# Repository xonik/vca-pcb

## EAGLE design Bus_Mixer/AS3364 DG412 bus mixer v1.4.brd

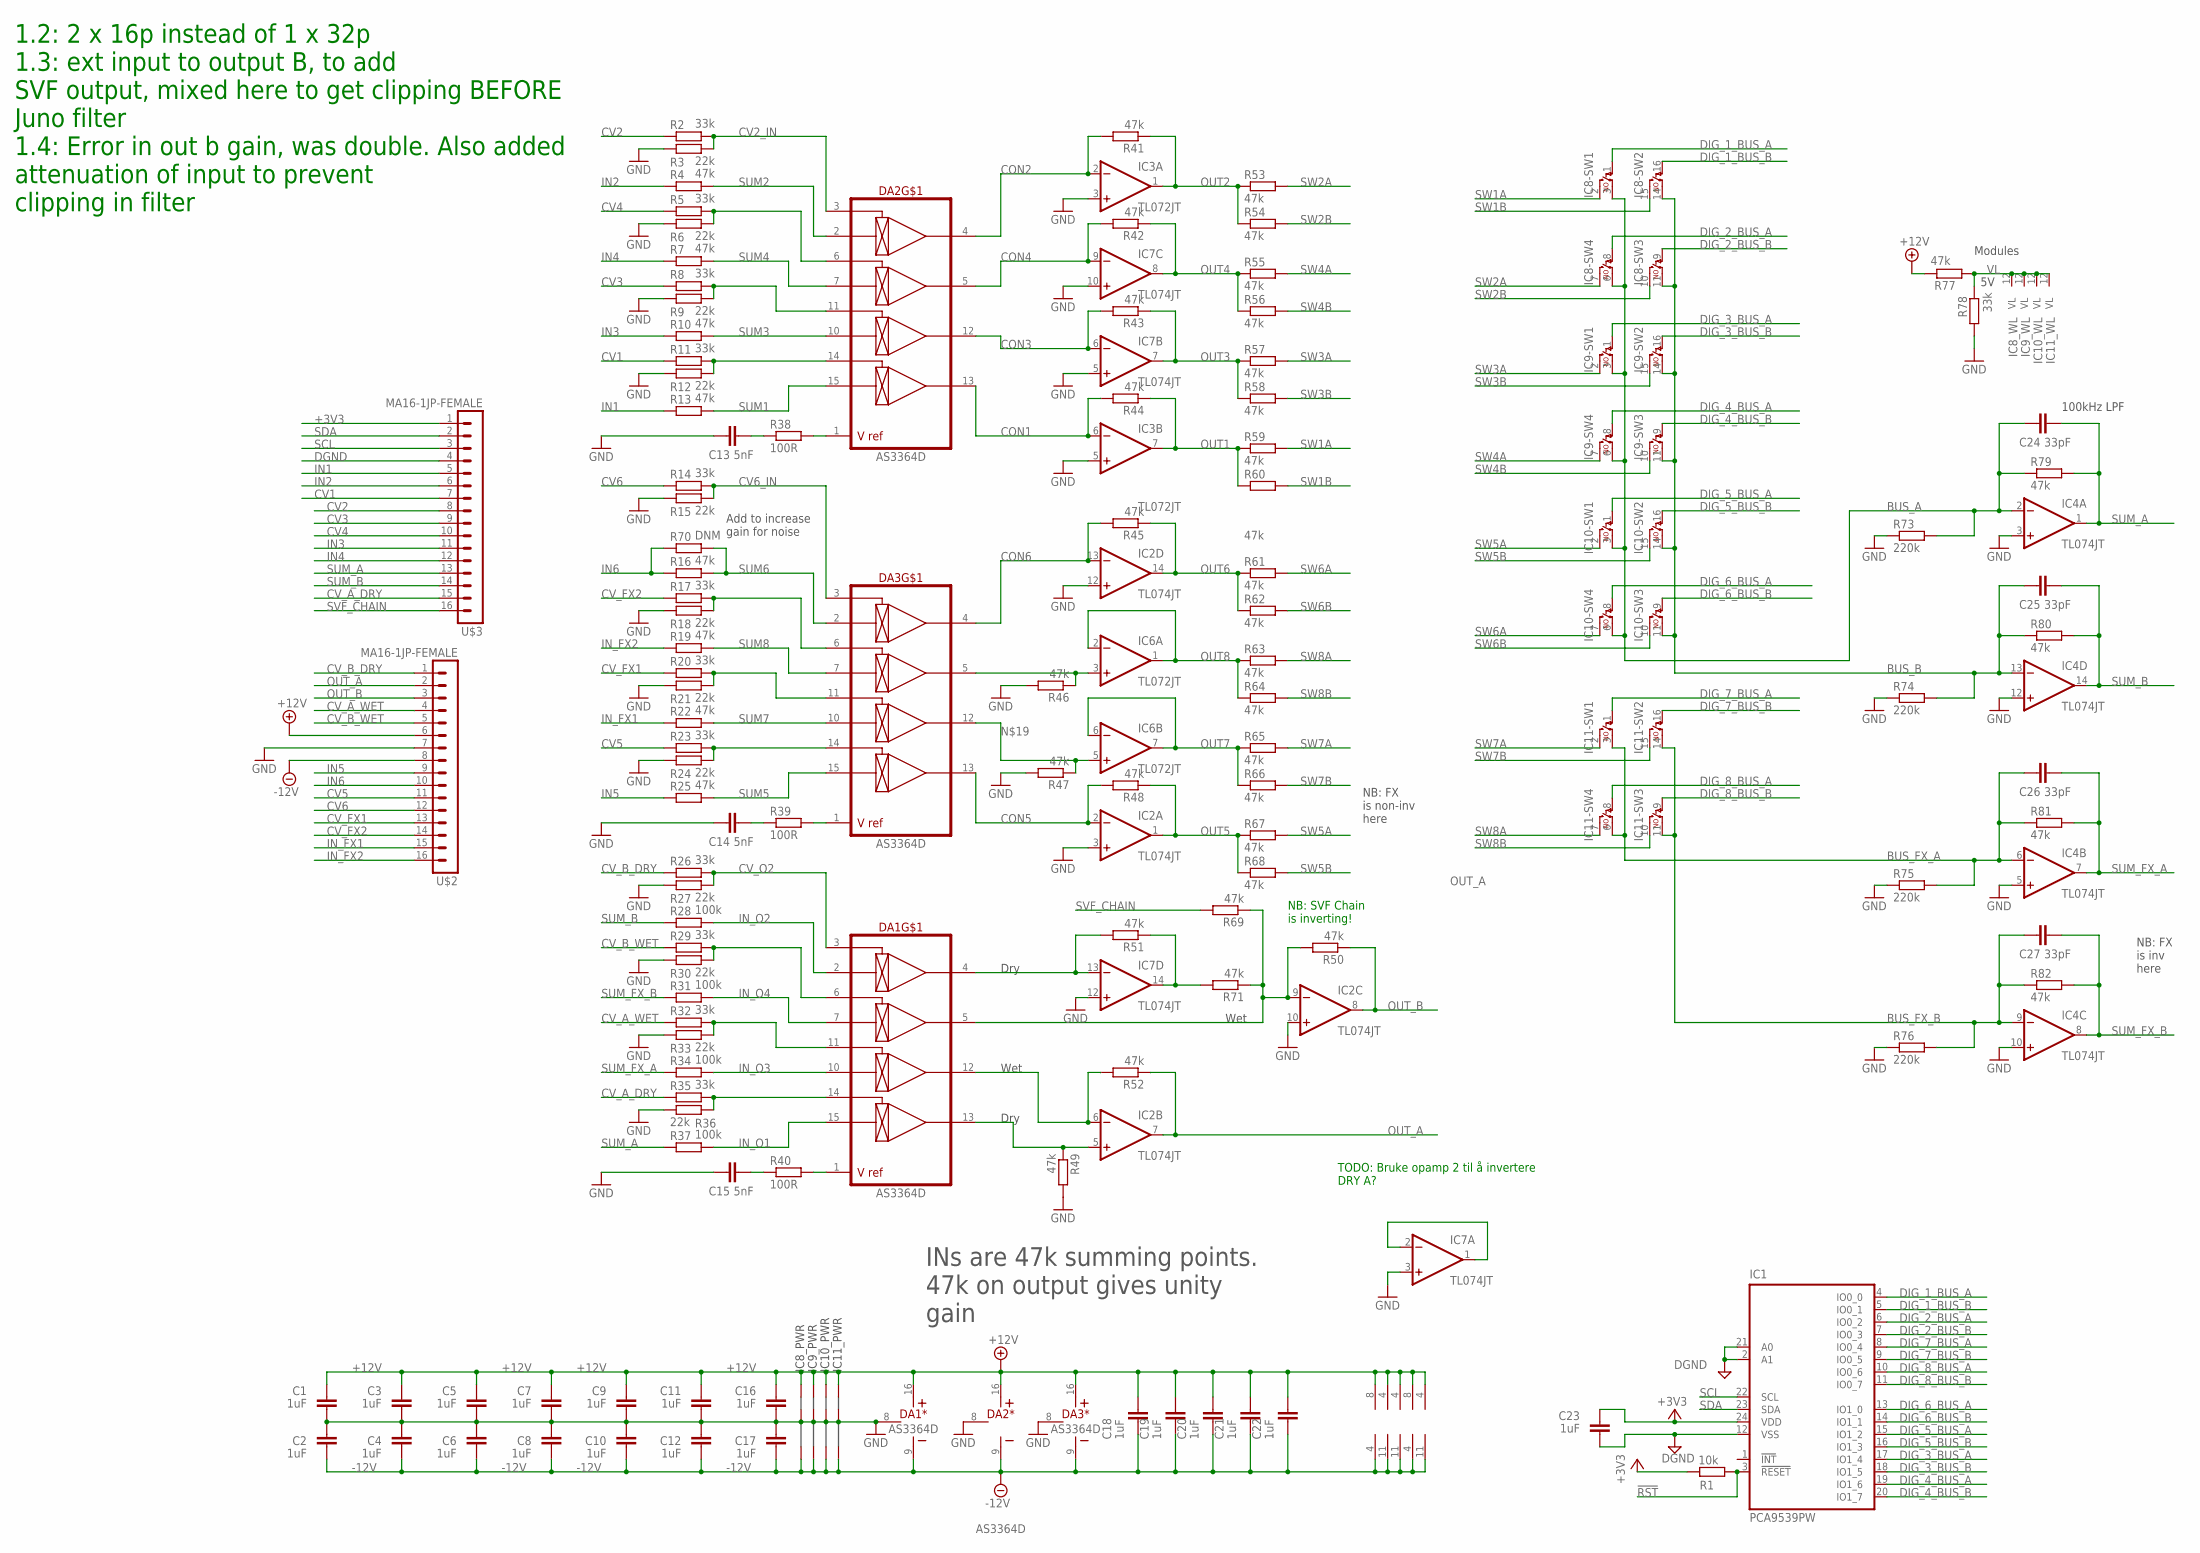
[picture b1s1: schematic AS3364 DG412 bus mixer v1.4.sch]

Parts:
C1, C2, C3, C4, C5, C6, C7, C8, C9, C10, C11, C12, C16, C17: 1uF; C0402-J
C13, C14, C15: 5nF; C0402-J
C18, C19, C20, C21, C22, C23: 1uF; C0402
C24, C25, C26, C27: 33pF; C0402-J
DA1, DA2, DA3: AS3364D; DIL16J
IC1: PCA9539PW; TSSOP24J
IC2, IC4, IC7: TL074JT; TSSOP14J
IC3, IC6: TL072JT; TSSOP8J
IC8, IC9, IC10, IC11: DG412-J; DIL16J
R1: 10k; R0402
R2, R5, R8, R11, R14, R17, R20, R23, R26, R29, R32, R35, R78: 33k; R0402
R3, R6, R9, R12, R15, R18, R21, R24, R27, R30, R33, R36: 22k; R0402
R4, R7, R10, R13, R16, R19, R22, R25, R41, R42, R43, R44, R45, R46, R47, R48, R49, R50, R51, R52, R53, R54, R55, R56, R57, R58, R59, R60, R61, R62, R63, R64, R65, R66, R67, R68, R69, R71, R77, R79, R80, R81, R82: 47k; R0402
R28, R31, R34, R37: 100k; R0402
R38, R39, R40: 100R; R0402
R70: DNM; R0805
R73, R74, R75, R76: 220k; R0603
U$2, U$3: MA16-1JP-FEMALE; SIP-PIN16-1J

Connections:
!RST: IC1.3 (!RESET), R1.2
+3V3: C23.2, IC1.24 (VDD), R1.1, U$3.1
+12V: C1.2, C3.2, C5.2, C7.2, C9.2, C11.2, C16.2, C18.2, C19.2, C20.2, C21.2, C22.2, DA1.16 (V+), DA2.16 (V+), DA3.16 (V+), IC2.4 (V+), IC3.8 (V+), IC4.4 (V+), IC6.8 (V+), IC7.4 (V+), IC8.13 (+15V), IC9.13 (+15V), IC10.13 (+15V), IC11.13 (+15V), R77.1, U$2.6
-12V: C2.1, C4.1, C6.1, C8.1, C10.1, C12.1, C17.1, C18.1, C19.1, C20.1, C21.1, C22.1, DA1.9 (V-), DA2.9 (V-), DA3.9 (V-), IC2.11 (V-), IC3.4 (V-), IC4.11 (V-), IC6.4 (V-), IC7.11 (V-), IC8.4 (-15V), IC9.4 (-15V), IC10.4 (-15V), IC11.4 (-15V), U$2.8
BUS_A: C24.1, IC4.2 (-IN), IC8.3 (S), IC8.6 (S), IC9.3 (S), IC9.6 (S), IC10.3 (S), IC10.6 (S), R73.2, R79.1
BUS_B: C25.1, IC4.13 (-IN), IC8.11 (S), IC8.14 (S), IC9.11 (S), IC9.14 (S), IC10.11 (S), IC10.14 (S), R74.2, R80.1
BUS_FX_A: C26.1, IC4.6 (-IN), IC11.3 (S), IC11.6 (S), R75.2, R81.1
BUS_FX_B: C27.1, IC4.9 (-IN), IC11.11 (S), IC11.14 (S), R76.2, R82.1
CON1: DA2.13 (OUT4), IC3.6 (-IN), R44.2
CON2: DA2.4 (OUT1), IC3.2 (-IN), R41.2
CON3: DA2.12 (OUT3), IC7.6 (-IN), R43.2
CON4: DA2.5 (OUT2), IC7.9 (-IN), R42.2
CON5: DA3.13 (OUT4), IC2.2 (-IN), R48.2
CON6: DA3.4 (OUT1), IC2.13 (-IN), R45.2
CON_O1: DA1.12 (OUT3), IC2.6 (-IN), R52.2
CV1: R11.1, U$3.7
CV2: R2.1, U$3.8
CV2_IN: DA2.3 (CV1), R2.2, R3.2
CV3: R8.1, U$3.9
CV4: R5.1, U$3.10
CV5: R23.1, U$2.11
CV6: R14.1, U$2.12
CV6_IN: DA3.3 (CV1), R14.2, R15.2
CV_A_DRY: R35.1, U$3.15
CV_A_WET: R32.1, U$2.4
CV_B_DRY: R26.1, U$2.1
CV_B_WET: R29.1, U$2.5
CV_FX1: R20.1, U$2.13
CV_FX2: R17.1, U$2.14
CV_O2: DA1.3 (CV1), R26.2, R27.2
DGND: C23.1, IC1.2 (A1), IC1.12 (VSS), IC1.21 (A0), U$3.4
DIG_1_BUS_A: IC1.4 (IO0_0), IC8.1 (C)
DIG_1_BUS_B: IC1.5 (IO0_1), IC8.16 (C)
DIG_2_BUS_A: IC1.6 (IO0_2), IC8.8 (C)
DIG_2_BUS_B: IC1.7 (IO0_3), IC8.9 (C)
DIG_3_BUS_A: IC1.17 (IO1_4), IC9.1 (C)
DIG_3_BUS_B: IC1.18 (IO1_5), IC9.16 (C)
DIG_4_BUS_A: IC1.19 (IO1_6), IC9.8 (C)
DIG_4_BUS_B: IC1.20 (IO1_7), IC9.9 (C)
DIG_5_BUS_A: IC1.15 (IO1_2), IC10.1 (C)
DIG_5_BUS_B: IC1.16 (IO1_3), IC10.16 (C)
DIG_6_BUS_A: IC1.13 (IO1_0), IC10.8 (C)
DIG_6_BUS_B: IC1.14 (IO1_1), IC10.9 (C)
DIG_7_BUS_A: IC1.8 (IO0_4), IC11.1 (C)
DIG_7_BUS_B: IC1.9 (IO0_5), IC11.16 (C)
DIG_8_BUS_A: IC1.10 (IO0_6), IC11.8 (C)
DIG_8_BUS_B: IC1.11 (IO0_7), IC11.9 (C)
GND: C1.1, C2.2, C3.1, C4.2, C5.1, C6.2, C7.1, C8.2, C9.1, C10.2, C11.1, C12.2, C13.1, C14.1, C15.1, C16.1, C17.2, DA1.8 (GND), DA2.8 (GND), DA3.8 (GND), IC2.3 (+IN), IC2.10 (+IN), IC2.12 (+IN), IC3.3 (+IN), IC3.5 (+IN), IC4.3 (+IN), IC4.5 (+IN), IC4.10 (+IN), IC4.12 (+IN), IC7.3 (+IN), IC7.5 (+IN), IC7.10 (+IN), IC7.12 (+IN), IC8.5 (AGND), IC9.5 (AGND), IC10.5 (AGND), IC11.5 (AGND), R3.1, R6.1, R9.1, R12.1, R15.1, R18.1, R21.1, R24.1, R27.1, R30.1, R33.1, R36.1, R46.2, R47.2, R49.2, R73.1, R74.1, R75.1, R76.1, R78.2, U$2.7
IN1: R13.1, U$3.5
IN2: R4.1, U$3.6
IN3: R10.1, U$3.11
IN4: R7.1, U$3.12
IN5: R25.1, U$2.9
IN6: R16.1, R70.1, U$2.10
IN_FX1: R22.1, U$2.15
IN_FX2: R19.1, U$2.16
IN_O1: DA1.15 (IN4), R37.2
IN_O2: DA1.2 (IN1), R28.2
IN_O3: DA1.10 (IN3), R34.2
IN_O4: DA1.7 (IN2), R31.2
unnamed: DA3.1 (VREF), R39.2
unnamed: DA2.1 (VREF), R38.2
unnamed: DA3.6 (CV2), R17.2, R18.2
unnamed: DA3.5 (OUT2), IC6.3 (+IN), R46.1
unnamed: DA3.11 (CV3), R20.2, R21.2
unnamed: DA1.5 (OUT2), IC2.9 (-IN), R50.2, R69.1, R71.1
unnamed: DA3.14 (CV4), R23.2, R24.2
unnamed: C14.2, R39.1
unnamed: DA1.1 (VREF), R40.2
unnamed: DA2.6 (CV2), R5.2, R6.2
unnamed: DA1.6 (CV2), R29.2, R30.2
unnamed: DA2.11 (CV3), R8.2, R9.2
unnamed: DA1.11 (CV3), R32.2, R33.2
unnamed: C13.2, R38.1
unnamed: DA1.14 (CV4), R35.2, R36.2
unnamed: C15.2, R40.1
unnamed: DA1.4 (OUT1), IC7.13 (-IN), R51.2
unnamed: DA1.13 (OUT4), IC2.5 (+IN), R49.1
unnamed: DA3.12 (OUT3), IC6.5 (+IN), R47.1
unnamed: IC7.14 (OUT), R51.1, R71.2
unnamed: DA2.14 (CV4), R11.2, R12.2
unnamed: IC7.1 (OUT), IC7.2 (-IN)
OUT1: IC3.7 (OUT), R44.1, R59.1, R60.1
OUT2: IC3.1 (OUT), R41.1, R53.1, R54.1
OUT3: IC7.7 (OUT), R43.1, R57.1, R58.1
OUT4: IC7.8 (OUT), R42.1, R55.1, R56.1
OUT5: IC2.1 (OUT), R48.1, R67.1, R68.1
OUT6: IC2.14 (OUT), R45.1, R61.1, R62.1
OUT7: IC6.6 (-IN), IC6.7 (OUT), R65.1, R66.1
OUT8: IC6.1 (OUT), IC6.2 (-IN), R63.1, R64.1
OUT_A: IC2.7 (OUT), R52.1, U$2.2
OUT_B: IC2.8 (OUT), R50.1, U$2.3
SCL: IC1.22 (SCL), U$3.3
SDA: IC1.23 (SDA), U$3.2
SUM1: DA2.15 (IN4), R13.2
SUM2: DA2.2 (IN1), R4.2
SUM3: DA2.10 (IN3), R10.2
SUM4: DA2.7 (IN2), R7.2
SUM5: DA3.15 (IN4), R25.2
SUM6: DA3.2 (IN1), R16.2, R70.2
SUM7: DA3.10 (IN3), R22.2
SUM8: DA3.7 (IN2), R19.2
SUM_A: C24.2, IC4.1 (OUT), R37.1, R79.2, U$3.13
SUM_B: C25.2, IC4.14 (OUT), R28.1, R80.2, U$3.14
SUM_FX_A: C26.2, IC4.7 (OUT), R34.1, R81.2
SUM_FX_B: C27.2, IC4.8 (OUT), R31.1, R82.2
SVF_CHAIN: R69.2, U$3.16
SW1A: IC8.2 (D), R59.2
SW1B: IC8.15 (D), R60.2
SW2A: IC8.7 (D), R53.2
SW2B: IC8.10 (D), R54.2
SW3A: IC9.2 (D), R57.2
SW3B: IC9.15 (D), R58.2
SW4A: IC9.7 (D), R55.2
SW4B: IC9.10 (D), R56.2
SW5A: IC10.2 (D), R67.2
SW5B: IC10.15 (D), R68.2
SW6A: IC10.7 (D), R61.2
SW6B: IC10.10 (D), R62.2
SW7A: IC11.2 (D), R65.2
SW7B: IC11.15 (D), R66.2
SW8A: IC11.7 (D), R63.2
SW8B: IC11.10 (D), R64.2
VL: IC8.12 (VL), IC9.12 (VL), IC10.12 (VL), IC11.12 (VL), R77.2, R78.1

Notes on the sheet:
INs are 47k summing points. 47k on output gives unity gain
Modules
100kHz LPF
Wet
Dry
NB: FX is non-inv here
NB: FX is inv here
1.2: 2 x 16p instead of 1 x 32p 1.3: ext input to output B, to add SVF output, mixed here to get clipping BEFORE Juno filter 1.4: Error in out b gain, was double. Also added attenuation of input to prevent clipping in filter
NB: SVF Chain is inverting!
Add to increase gain for noise
TODO: Bruke opamp 2 til å invertere DRY A?

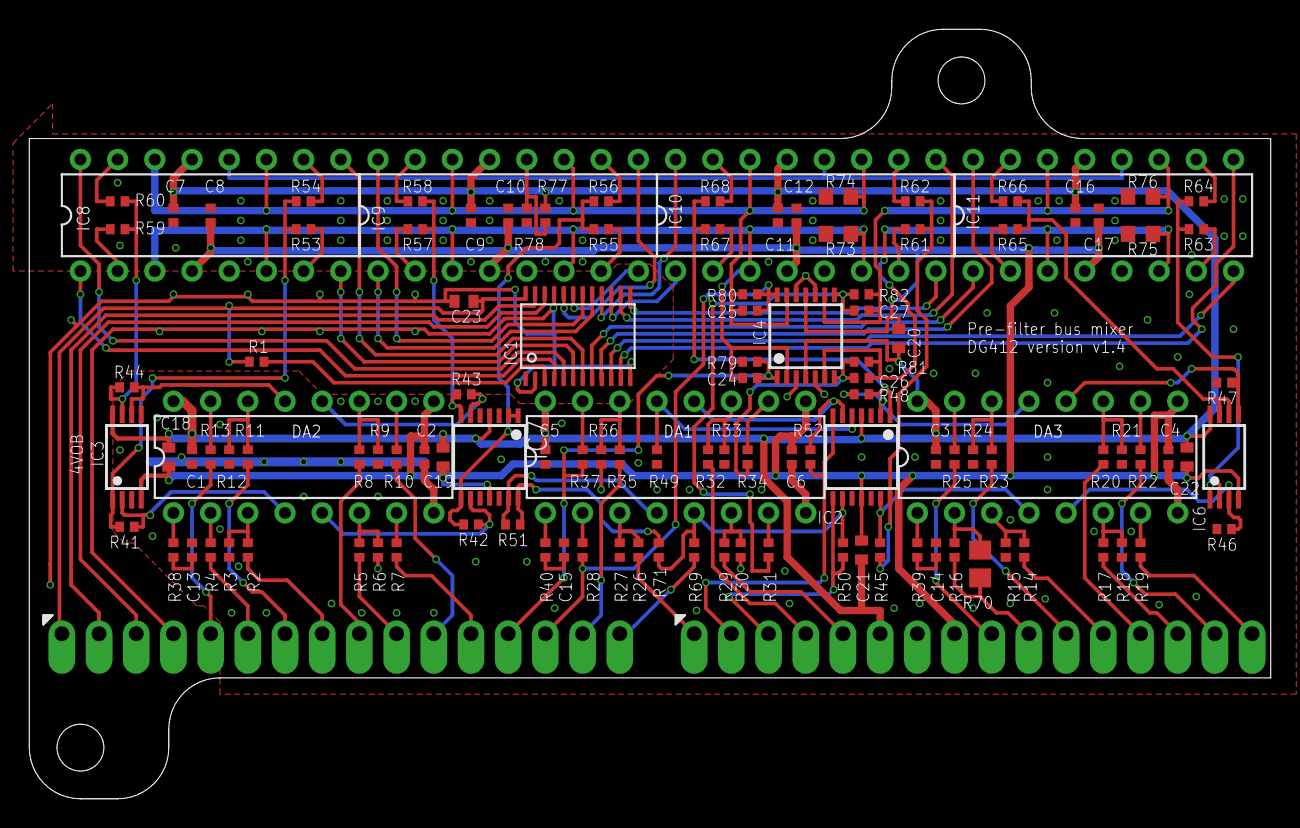
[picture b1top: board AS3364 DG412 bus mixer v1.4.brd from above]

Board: 2 copper layers, 84.8 x 52.5 mm, 124 parts (1 on the bottom side), 124 nets.

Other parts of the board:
U$1: XONIK_LOGO_35

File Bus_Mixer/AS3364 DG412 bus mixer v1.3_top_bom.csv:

Comment,Designator,Footprint,LCSC Part #
1uF,C1 C2 C3 C4 C5 C6 C7 C8 C9 C10 C11 C12 C16 C17,C0402-J,
1uF,C18 C19 C20 C21 C22 C23,C0402,
5nF,C13 C14 C15,C0402-J,
10k,R1,R0402,
22k,R3 R6 R9 R12 R15 R18 R21 R24 R27 R30 R33 R36,R0402,
33k,R2 R5 R8 R11 R14 R17 R20 R23 R26 R29 R32 R35 R78,R0402,
33pF,C24 C25 C26 C27,C0402-J,
47k,R4 R7 R10 R13 R16 R19 R22 R25 R28 R31 R34 R37 R41 R42 R43 R44 R45 R46 R47 R48 R49 R50 R51 R52 R53 R54 R55 R56 R57 R58 R59 R60 R61 R62 R63 R64 R65 R66 R67 R68 R69 R77 R79 R80 R81 R82,R0402,
100R,R38 R39 R40,R0402,
220k,R73 R74 R75 R76,R0603,
AS3364D,DA1 DA2 DA3,DIL16J,
DG412-J,IC8 IC9 IC10 IC11,DIL16J,
DNM,R70,R0805,
MA16-1JP-FEMALE,U$2 U$3,SIP-PIN16-1J,
PCA9539PW,IC1,TSSOP24J,
TL072JT,IC3 IC5 IC6,TSSOP8J,
TL074JT,IC2 IC4,TSSOP14J,

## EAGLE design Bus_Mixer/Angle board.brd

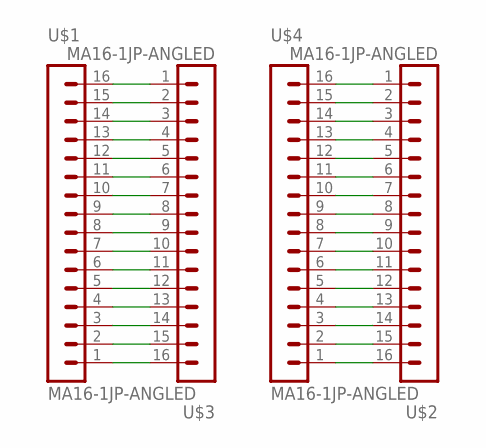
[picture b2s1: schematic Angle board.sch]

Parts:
U$1, U$2, U$3, U$4: MA16-1JP-ANGLED; SIP-PIN16-1J

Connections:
AGND: U$1.7, U$2.4, U$3.10, U$4.13
unnamed: U$1.1, U$3.16
unnamed: U$1.2, U$3.15
unnamed: U$1.3, U$3.14
unnamed: U$1.4, U$3.13
unnamed: U$1.5, U$3.12
unnamed: U$1.6, U$3.11
unnamed: U$1.8, U$3.9
unnamed: U$1.9, U$3.8
unnamed: U$1.10, U$3.7
unnamed: U$1.11, U$3.6
unnamed: U$1.12, U$3.5
unnamed: U$1.13, U$3.4
unnamed: U$1.14, U$3.3
unnamed: U$1.15, U$3.2
unnamed: U$1.16, U$3.1
unnamed: U$2.16, U$4.1
unnamed: U$2.15, U$4.2
unnamed: U$2.14, U$4.3
unnamed: U$2.13, U$4.4
unnamed: U$2.12, U$4.5
unnamed: U$2.11, U$4.6
unnamed: U$2.10, U$4.7
unnamed: U$2.9, U$4.8
unnamed: U$2.8, U$4.9
unnamed: U$2.7, U$4.10
unnamed: U$2.6, U$4.11
unnamed: U$2.5, U$4.12
unnamed: U$2.3, U$4.14
unnamed: U$2.2, U$4.15
unnamed: U$2.1, U$4.16

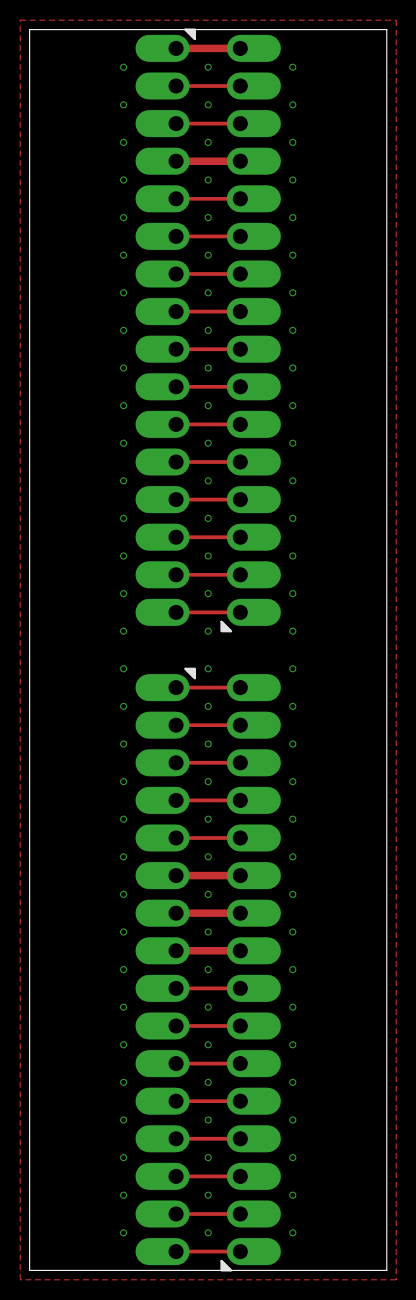
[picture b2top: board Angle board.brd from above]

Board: 2 copper layers, 24.1 x 83.8 mm, 5 parts (1 on the bottom side), 31 nets.

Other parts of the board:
U$5: XONIK_LOGO_18

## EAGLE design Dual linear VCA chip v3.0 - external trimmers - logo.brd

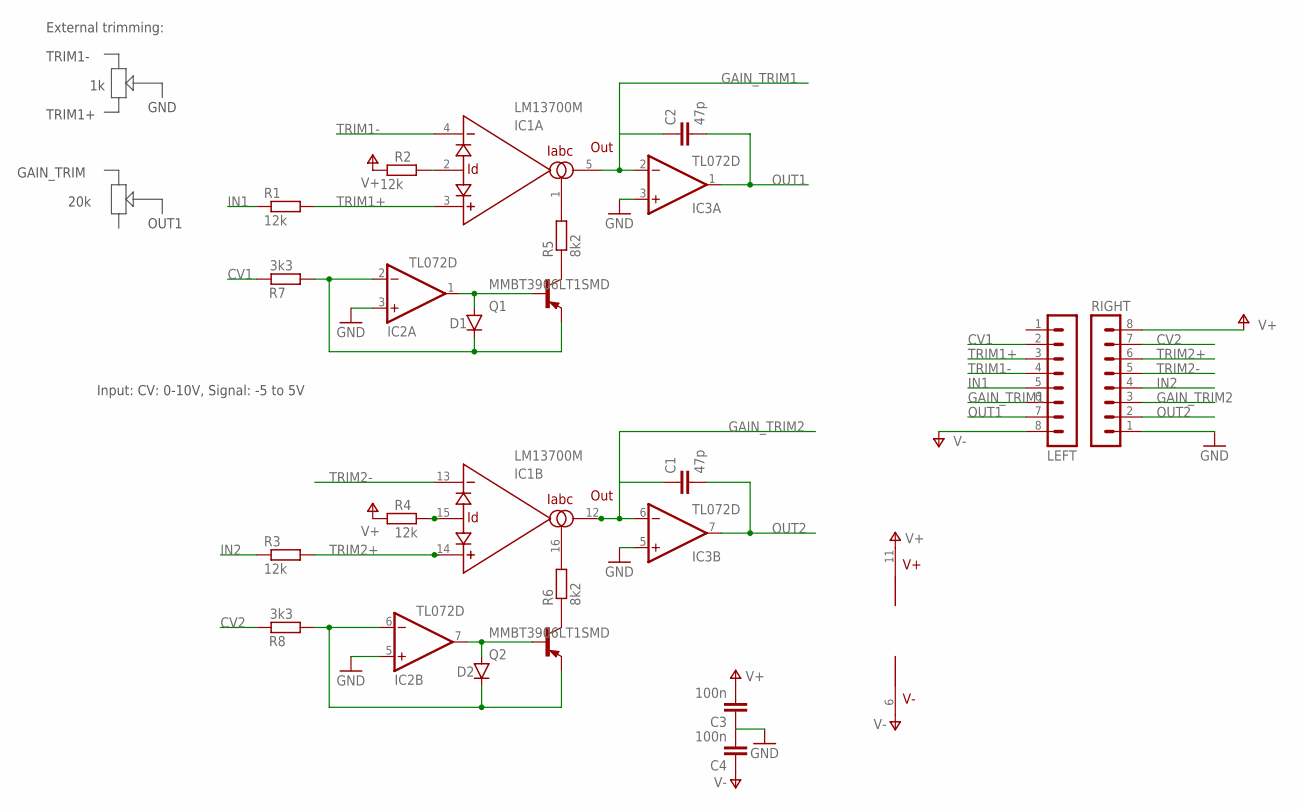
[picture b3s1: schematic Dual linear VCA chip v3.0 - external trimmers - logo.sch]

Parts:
C1, C2: 47p; C0805
C3, C4: 100n; C0805
D1, D2: 1N41480805; D0805-J
IC1: LM13700M; SO16
IC2, IC3: TL072D; SO08
LEFT: MA08-1JC; MA08-1J
Q1, Q2: MMBT3906LT1SMD; SOT23-BEC
R1, R2, R3, R4: 12k; R0805
R5, R6: 8k2; R0805
R7, R8: 3k3; R0805
RIGHT: MA08-1JC; MA08-1J

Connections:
CV1: LEFT.2, R7.2
CV2: R8.2, RIGHT.7
GAIN_TRIM1: C2.1, IC1.5 (OUT), IC3.2 (-IN), LEFT.6
GAIN_TRIM2: C1.1, IC1.12 (OUT), IC3.6 (-IN), RIGHT.3
GND: C3.1, C4.2, IC2.3 (+IN), IC2.5 (+IN), IC3.3 (+IN), IC3.5 (+IN), RIGHT.1
IN1: LEFT.5, R1.1
IN2: R3.1, RIGHT.4
unnamed: Q1.C, R5.1
unnamed: Q2.C, R6.1
unnamed: D1.C, IC2.2 (-IN), Q1.E, R7.1
unnamed: IC1.1 (IABC), R5.2
unnamed: IC1.2 (ID), R2.2
unnamed: D2.A, IC2.7 (OUT), Q2.B
unnamed: D1.A, IC2.1 (OUT), Q1.B
unnamed: D2.C, IC2.6 (-IN), Q2.E, R8.1
unnamed: IC1.16 (IABC), R6.2
unnamed: IC1.15 (ID), R4.2
OUT1: C2.2, IC3.1 (OUT), LEFT.7
OUT2: C1.2, IC3.7 (OUT), RIGHT.2
TRIM1+: IC1.3 (+IN), LEFT.3, R1.2
TRIM1-: IC1.4 (-IN), LEFT.4
TRIM2+: IC1.14 (+IN), R3.2, RIGHT.6
TRIM2-: IC1.13 (-IN), RIGHT.5
V+: C3.2, IC1.11 (V+), IC2.8 (V+), IC3.8 (V+), R2.1, R4.1, RIGHT.8
V-: C4.1, IC1.6 (V-), IC2.4 (V-), IC3.4 (V-), LEFT.8

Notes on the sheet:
Input: CV: 0-10V, Signal: -5 to 5V
TRIM1-
TRIM1+
GND
External trimming:
GAIN_TRIM
OUT1
20k

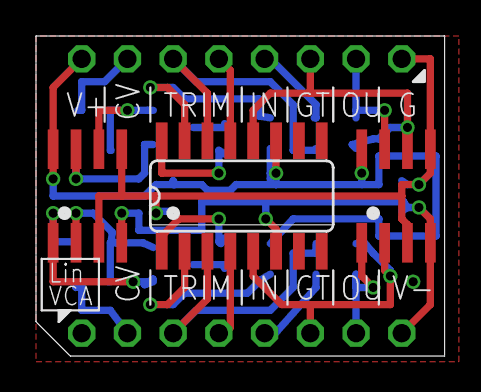
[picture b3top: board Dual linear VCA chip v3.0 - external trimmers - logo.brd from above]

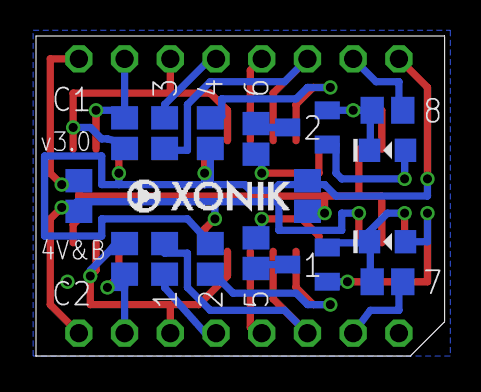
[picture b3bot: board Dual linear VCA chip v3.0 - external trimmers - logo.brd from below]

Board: 2 copper layers, 22.7 x 17.8 mm, 21 parts (16 on the bottom side), 25 nets.

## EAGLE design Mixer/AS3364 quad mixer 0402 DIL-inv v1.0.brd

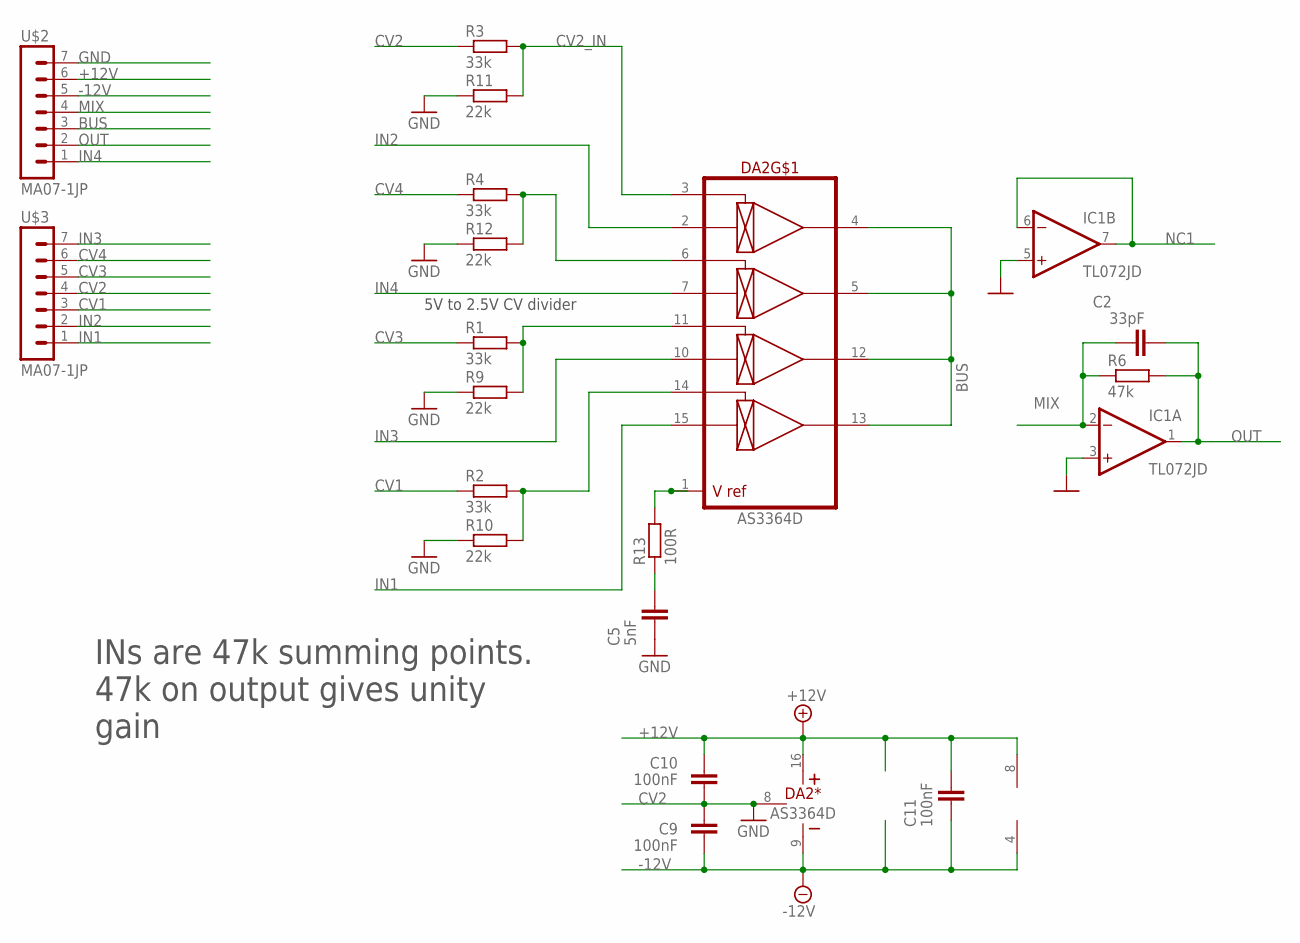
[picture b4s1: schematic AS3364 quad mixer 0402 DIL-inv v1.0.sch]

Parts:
C2: 33pF; C0402
C5: 5nF; C0402
C9, C10, C11: 100nF; C0402
DA2: AS3364D; DIL16J
IC1: TL072JD; SO08J
R1, R2, R3, R4: 33k; R0402
R6: 47k; R0402
R9, R10, R11, R12: 22k; R0402
R13: 100R; R0402
U$2, U$3: MA07-1JP; SIP-PIN07-1J

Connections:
+12V: C10.2, C11.2, DA2.16 (V+), IC1.8 (V+), U$2.6
-12V: C9.1, C11.1, DA2.9 (V-), IC1.4 (V-), U$2.5
BUS: DA2.4 (OUT1), DA2.5 (OUT2), DA2.12 (OUT3), DA2.13 (OUT4), U$2.3
CV1: R2.1, U$3.3
CV2: R3.1, U$3.4
CV2_IN: DA2.3 (CV1), R3.2, R11.2
CV3: R1.1, U$3.5
CV4: R4.1, U$3.6
GND: C5.1, C9.2, C10.1, DA2.8 (GND), IC1.3 (+IN), IC1.5 (+IN), R9.1, R10.1, R11.1, R12.1, U$2.7
IN1: DA2.15 (IN4), U$3.1
IN2: DA2.2 (IN1), U$3.2
IN3: DA2.10 (IN3), U$3.7
IN4: DA2.7 (IN2), U$2.1
MIX: C2.1, IC1.2 (-IN), R6.1, U$2.4
unnamed: DA2.1 (VREF), R13.2
unnamed: DA2.6 (CV2), R4.2, R12.2
unnamed: DA2.11 (CV3), R1.2, R9.2
unnamed: C5.2, R13.1
unnamed: DA2.14 (CV4), R2.2, R10.2
NC1: IC1.6 (-IN), IC1.7 (OUT)
OUT: C2.2, IC1.1 (OUT), R6.2, U$2.2

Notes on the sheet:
INs are 47k summing points. 47k on output gives unity gain
5V to 2.5V CV divider

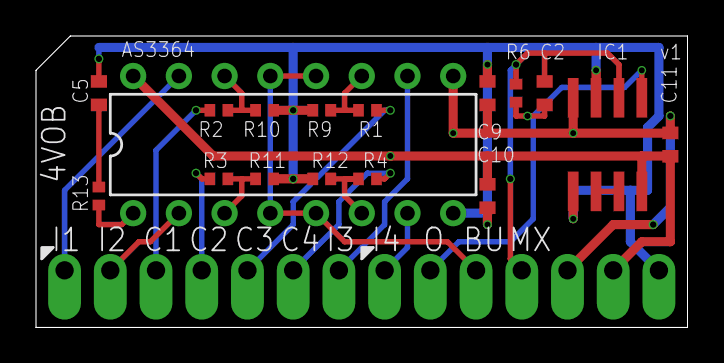
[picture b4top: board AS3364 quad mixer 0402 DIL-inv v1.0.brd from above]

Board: 2 copper layers, 36.2 x 16.2 mm, 20 parts (1 on the bottom side), 21 nets.

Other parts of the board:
U$1: XONIK_LOGO_18
